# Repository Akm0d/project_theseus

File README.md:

# Project Theseus
This project is forked from the private repo of the OpenWest Defusal Station project. It is named "Project Theseus" after the paradox of the Ship of Theseus; a thought experiment that raises the question of whether an object that has had all of its components replaced remains fundamentally the same object.

# Contribution Guidelines
1. Create a branch for your code and merge it to master once the changes are stable
2. Keep the file structure as organized as possible
3. Never commit binaries, hidden files created by your IDE, or Windows-style line endings.
4. Keep detailed comments of what each function is meant to do
5. Follow the PEP-8 standard when writing python https://www.python.org/dev/peps/pep-0008/
6. Use comments starting with TODO to mark a feature that needs to be implemented and FIXME to mark features that need to be improved
7. If you are stuck, then it is absolutely OK to ask for help

# Getting Started
```bash
$ sudo apt-get update
$ sudo apt-get install python3 git python3-pip
$ git clone https://github.com/jtylers/project_theseus.git
$ cd project_theseus
$ git submodule update --init
$ pip3 install -r requirements.txt
$ ./serve.py
$ firefox 127.0.0.1:5000
```
I highly suggest using PyCharm if you are working with Flask and Python
```bash
$ sudo apt-get update
$ sudo apt-get install snapd
$ snap install pycharm-community
```
Add the project root to your python path for things to run correctly
```bash
$ echo "export PYTHONPATH=$PYTHONPATH:$HOME/project_theseus" >> ~/.profile
$ source ~/.profile
```

## Raspberry pi - ARCH Linux Setup
```bash
$ ## login with user: root password: root
$ # Delete default user
$ userdel alarm
$ # Create a new adminuser
$ useradd admin
$ # Set password for admin
$ passwd admin
$ # Make a home folder for admin
$ mkdir -p /home/admin
$ # Change ownership of the admin's home folder
$ chown -R admin:admin /home/admin
$ pacman -S sudo
$ # Grant admin sudo privileges
$ visudo
$ ## Press SHIFT + G then SHIFT + A
$ ## type "admin ALL=(ALL) ALL" without the quotes
$ ## save and quit by pressing ESCAPE, typing ":x" and pressing ENTER
$ # Remove root's password entry so that you can only log in as "admin" and use sudo and to do root stuff
$ vim /etc/shadow
$ ## replace root's password hash with !
$ # Install dependencies
$ pacman -S fakeroot gcc git i2c-tools make nginx packer python python-dateutil python-flask python-flask-restful python-pip tmux vim 
$ packer -S raspi-config
$ # Enable I2C 
$ echo "dtparam=i2c_arm=on"| sudo tee -a /boot/config.txt
$ sudo reboot
$ ## Log in as admin
$ ## Allow admin to access i2c
$ sudo chown admin:admin /dev/i2c*
$ ## Proceed with the instructions from the "Getting Started" section
$ ## Run project_theseus/pi_setup.sh
```

## Where are variables stored?
Stored in the database
```
ID
Name
Laser   -- Deprecated
Code
Color
Time    -- Stored as a datetime object but written at end of game
Success
```

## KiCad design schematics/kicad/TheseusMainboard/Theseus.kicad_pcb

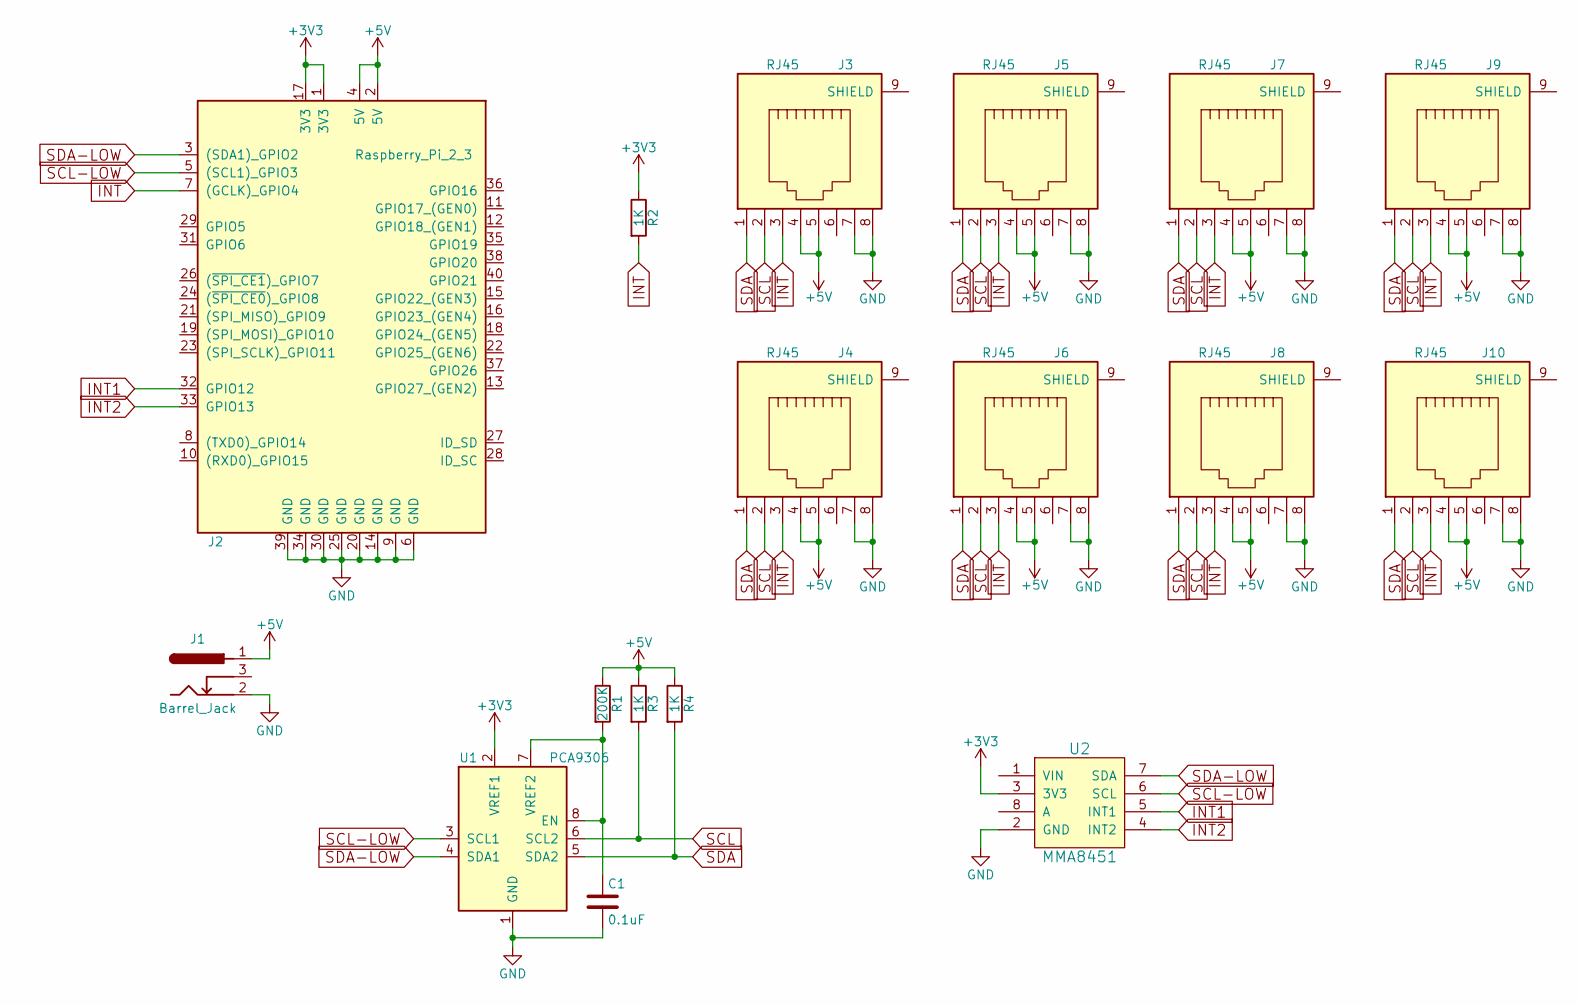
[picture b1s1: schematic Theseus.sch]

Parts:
C1: 0.1uF; C_0805_HandSoldering
J1: Barrel_Jack; POWER_JACK_PTH
J2: Raspberry_Pi_2_3; Pin_Header_Straight_2x20
J3, J4, J5, J6, J7, J8, J9, J10: RJ45; RJ45-8
R1: 200K; R_0805_HandSoldering
R2, R3, R4: 1K; R_0805_HandSoldering
U1: PCA9306; SO08
U2: MMA8451; Pin_Header_Straight_1x08_Pitch2.54mm

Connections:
+3V3: J2.1 (3V3), J2.17 (3V3), R2.1, U1.2 (VREF1), U2.3 (3V3)
+5V: J1.1, J2.2 (5V), J2.4 (5V), J3.4, J3.5, J4.4, J4.5, J5.4, J5.5, J6.4, J6.5, J7.4, J7.5, J8.4, J8.5, J9.4, J9.5, J10.4, J10.5, R1.1, R3.1, R4.1
GND: C1.2, J1.2, J2.6 (GND), J2.9 (GND), J2.14 (GND), J2.20 (GND), J2.25 (GND), J2.30 (GND), J2.34 (GND), J2.39 (GND), J3.7, J3.8, J4.7, J4.8, J5.7, J5.8, J6.7, J6.8, J7.7, J7.8, J8.7, J8.8, J9.7, J9.8, J10.7, J10.8, U1.1 (GND), U2.2 (GND)
INT: J2.7 ((GCLK)_GPIO4), J3.3, J4.3, J5.3, J6.3, J7.3, J8.3, J9.3, J10.3, R2.2
INT1: J2.32 (GPIO12), U2.5 (INT1)
INT2: J2.33 (GPIO13), U2.4 (INT2)
unnamed: C1.1, R1.2, U1.7 (VREF2), U1.8 (EN)
SCL: J3.2, J4.2, J5.2, J6.2, J7.2, J8.2, J9.2, J10.2, R3.2, U1.6 (SCL2)
SCL-LOW: J2.5 ((SCL1)_GPIO3), U1.3 (SCL1), U2.6 (SCL)
SDA: J3.1, J4.1, J5.1, J6.1, J7.1, J8.1, J9.1, J10.1, R4.2, U1.5 (SDA2)
SDA-LOW: J2.3 ((SDA1)_GPIO2), U1.4 (SDA1), U2.7 (SDA)

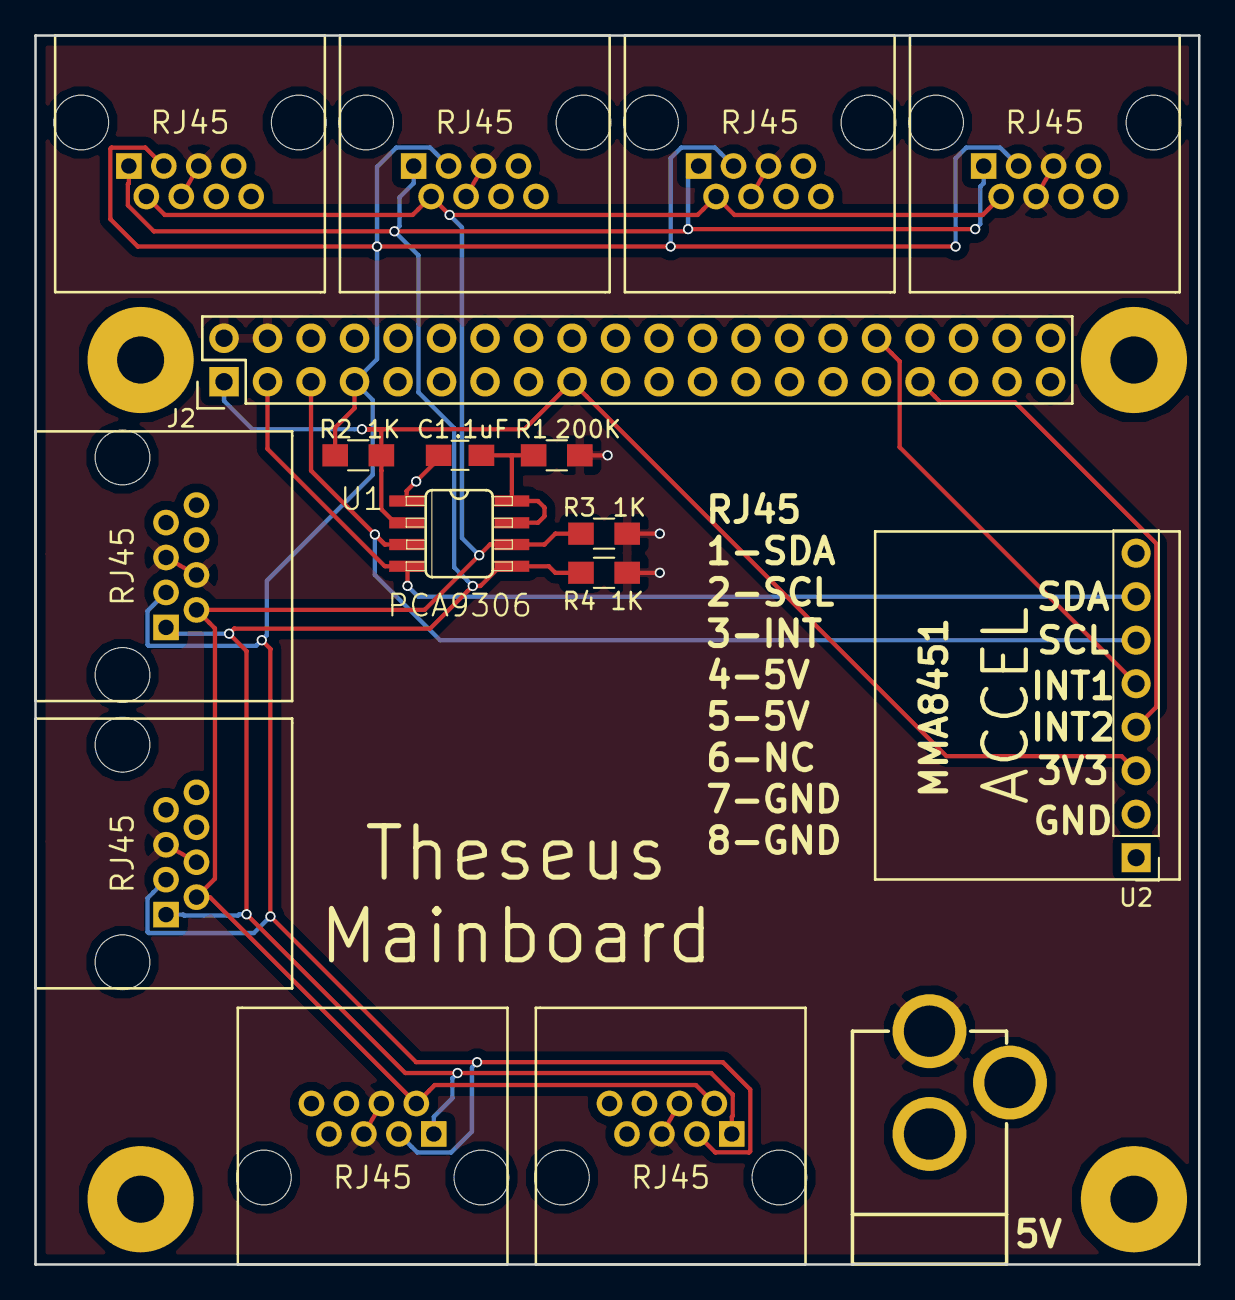
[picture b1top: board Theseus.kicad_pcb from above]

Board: 2 copper layers, 67.9 x 71.8 mm, 17 parts (0 on the bottom side), 11 nets.

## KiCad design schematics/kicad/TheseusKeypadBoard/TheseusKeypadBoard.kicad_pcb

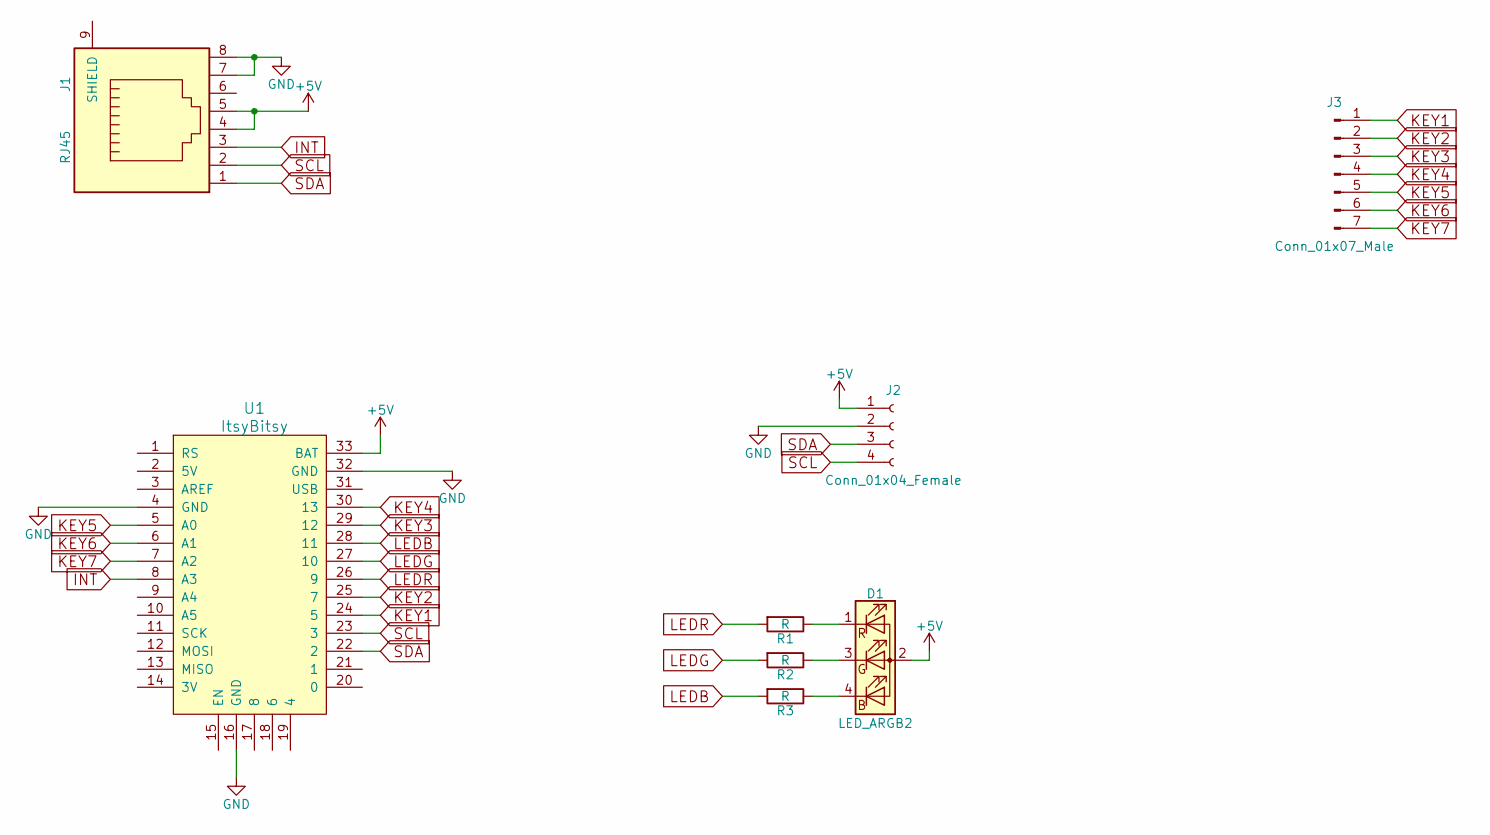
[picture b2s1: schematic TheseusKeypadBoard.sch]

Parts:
D1: LED_ARGB2
J1: RJ45; RJ45-8
J2: Conn_01x04_Female; Pin_Header_Straight_1x04_Pitch2.54mm
J3: Conn_01x07_Male; Pin_Header_Straight_1x07_Pitch2.54mm
R1, R2, R3: R; R_0805_HandSoldering
U1: ItsyBitsy

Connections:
+5V: D1.2 (A), J1.4, J1.5, J2.1, U1.33 (BAT)
GND: J1.7, J1.8, J2.2, U1.4 (GND), U1.16 (GND), U1.32 (GND)
INT: J1.3, U1.8 (A3)
KEY1: J3.1, U1.24 (5)
KEY2: J3.2, U1.25 (7)
KEY3: J3.3, U1.29 (12)
KEY4: J3.4, U1.30 (13)
KEY5: J3.5, U1.5 (A0)
KEY6: J3.6, U1.6 (A1)
KEY7: J3.7, U1.7 (A2)
LEDB: R3.2, U1.28 (11)
LEDG: R2.2, U1.27 (10)
LEDR: R1.2, U1.26 (9)
unnamed: D1.1 (RK), R1.1
unnamed: D1.3 (GK), R2.1
unnamed: D1.4 (BK), R3.1
SCL: J1.2, J2.4, U1.23 (3)
SDA: J1.1, J2.3, U1.22 (2)

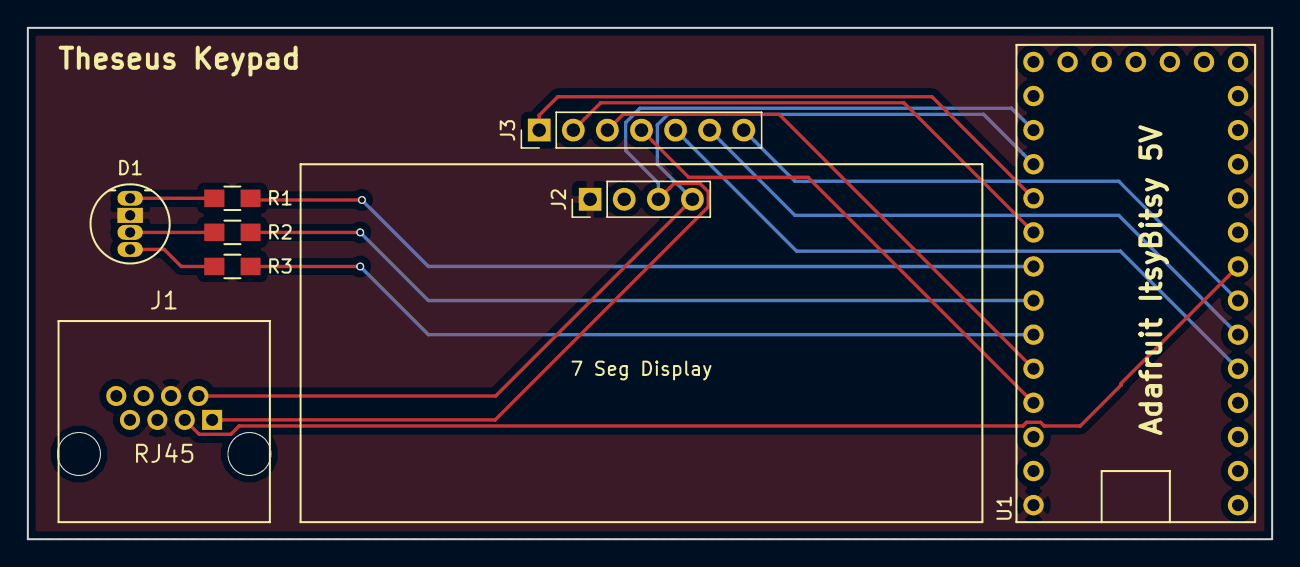
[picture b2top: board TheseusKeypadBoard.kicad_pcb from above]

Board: 2 copper layers, 92.7 x 38.1 mm, 8 parts (0 on the bottom side), 18 nets.

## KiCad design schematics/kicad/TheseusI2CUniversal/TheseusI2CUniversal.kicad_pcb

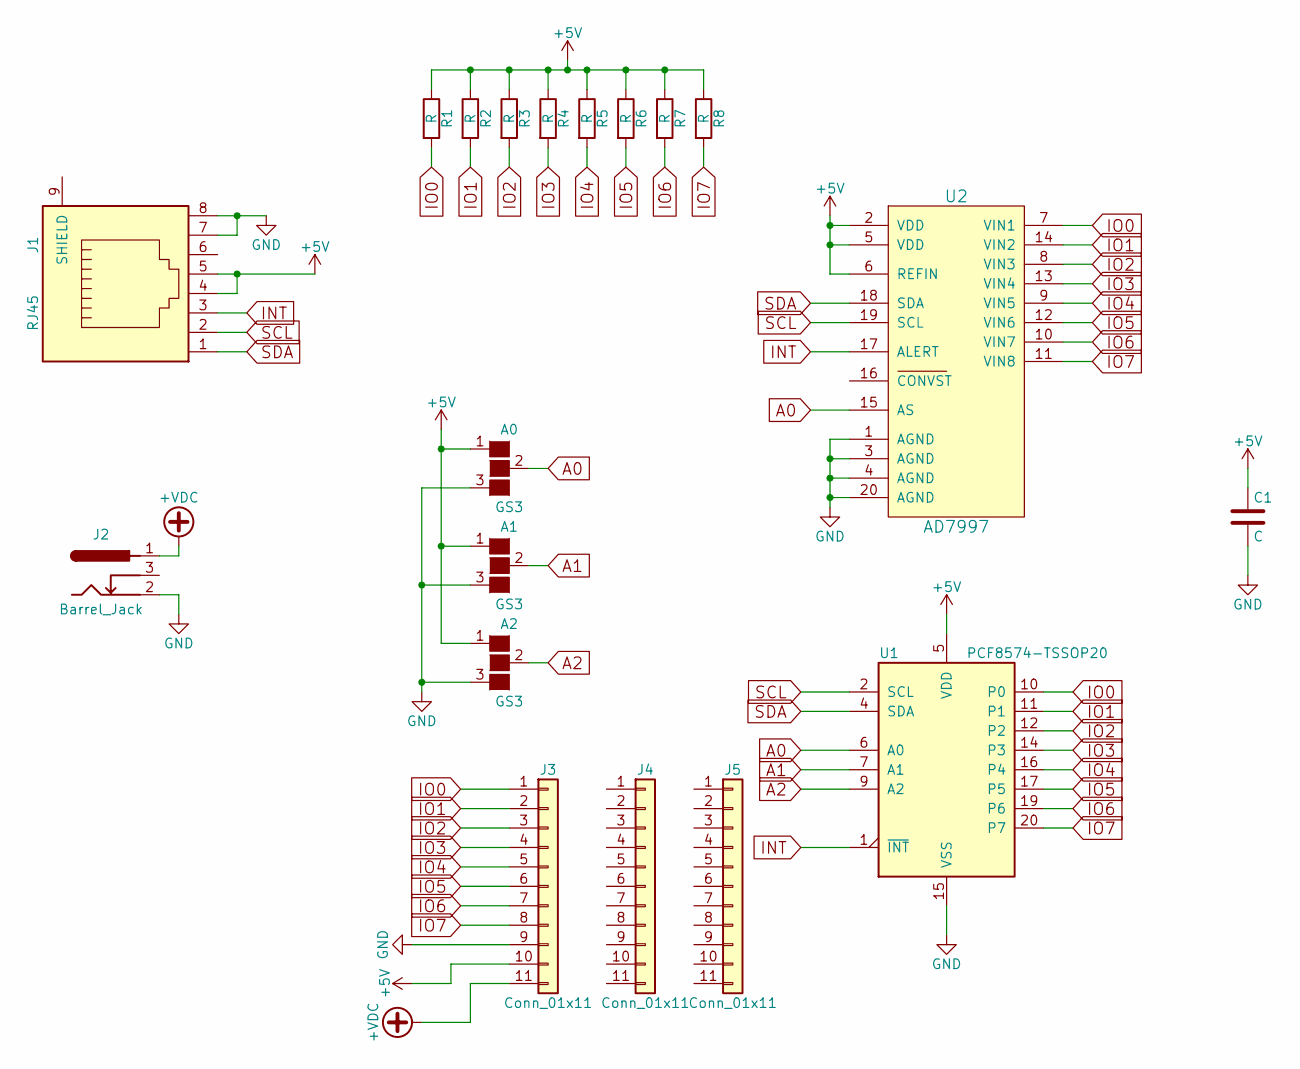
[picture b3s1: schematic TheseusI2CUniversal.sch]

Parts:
A0, A1, A2: GS3
C1: C; C_0805_HandSoldering
J1: RJ45; RJ45-8
J2: Barrel_Jack; POWER_JACK_PTH
J3, J4, J5: Conn_01x11; Socket_Strip_Straight_1x11_Pitch2.54mm
R1, R2, R3, R4, R5, R6, R7, R8: R; R_0805_HandSoldering
U1: PCF8574-TSSOP20; TSSOP20
U2: AD7997; TSSOP20

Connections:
+5V: A0.1 (G1), A1.1 (G1), A2.1 (G1), C1.1, J1.4, J1.5, J3.10, R1.1, R2.1, R3.1, R4.1, R5.1, R6.1, R7.1, R8.1, U1.5 (VDD), U2.2 (VDD), U2.5 (VDD), U2.6 (REFIN)
+VDC: J2.1, J3.11
A0: A0.2 (G2), U1.6 (A0), U2.15 (AS)
A1: A1.2 (G2), U1.7 (A1)
A2: A2.2 (G2), U1.9 (A2)
GND: A0.3 (G3), A1.3 (G3), A2.3 (G3), C1.2, J1.7, J1.8, J2.2, J3.9, U1.15 (VSS), U2.1 (AGND), U2.3 (AGND), U2.4 (AGND), U2.20 (AGND)
INT: J1.3, U1.1 (~INT~), U2.17 (ALERT)
IO0: J3.1, R1.2, U1.10 (P0), U2.7 (VIN1)
IO1: J3.2, R2.2, U1.11 (P1), U2.14 (VIN2)
IO2: J3.3, R3.2, U1.12 (P2), U2.8 (VIN3)
IO3: J3.4, R4.2, U1.14 (P3), U2.13 (VIN4)
IO4: J3.5, R5.2, U1.16 (P4), U2.9 (VIN5)
IO5: J3.6, R6.2, U1.17 (P5), U2.12 (VIN6)
IO6: J3.7, R7.2, U1.19 (P6), U2.10 (VIN7)
IO7: J3.8, R8.2, U1.20 (P7), U2.11 (VIN8)
SCL: J1.2, U1.2 (SCL), U2.19 (SCL)
SDA: J1.1, U1.4 (SDA), U2.18 (SDA)

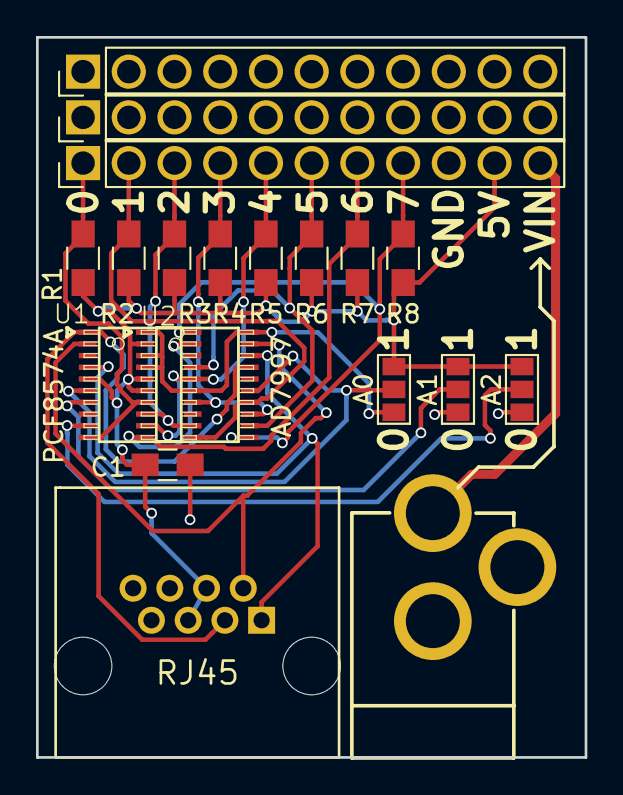
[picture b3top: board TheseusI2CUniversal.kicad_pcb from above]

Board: 2 copper layers, 30.5 x 40.0 mm, 19 parts (0 on the bottom side), 17 nets.

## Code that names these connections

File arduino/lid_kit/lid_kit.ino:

// Arduino code for project theseus
// Kristian Sims

#include <Keypad.h>
#include <Wire.h>

#define I2C_ADDRESS 0x69
#define KEYPAD_REGISTER = 0x23

// Set up keypad
#define NROWS 4
#define NCOLS 3
char keys[NROWS][NCOLS] = {
  {'1', '2', '3'},
  {'4', '5', '6'},
  {'7', '8', '9'},
  {'*', '0', '#'}
};
byte rows_pins[NROWS] = {5, 7, 12, 13};
byte cols_pins[NCOLS] = {A0, A1, A2};
Keypad keypad = Keypad(makeKeymap(keys), rows_pins, cols_pins, NROWS, NCOLS);

// Keypress buffer
#define BUFLEN 16
char key_buffer[BUFLEN];
int buffer_count = 0;

// LED Pins and 8-bit color scaling (which I made up, feel free to tweak)
#define LEDR 9
#define LEDG 10
#define LEDB 11

// Color maps for 8-bit color (vaguely logarithmic). Duty cycle is (255-x)/255.
byte led2bit[4] = {255, 191, 127, 0};  // 0%, 25%, 50%, 100%
byte led3bit[8] = {255, 223, 191, 159, 127, 63, 0, 0}; // w/e


void setup() {
  // Set up I2C as a slave
  Wire.begin(I2C_ADDRESS);
  Wire.onRequest(i2c_request);
  Wire.onReceive(i2c_receive);
  // Set up keypad. If you get duplicate keypress, increase debounce time. >200 is too much.
  keypad.setDebounceTime(50);
  keypad.addEventListener(keypad_event);
  Serial.begin(115200);
}

void loop() {
  keypad.getKey();
}

// On I2C read, return buffered characters, or a single "." for no keypress
void i2c_request() {
  Serial.write("KEY: ");
  if (buffer_count > 0) {
    Wire.write(key_buffer);
    Serial.write(key_buffer);
    // Clear buffer so string termination is automatic
    while (buffer_count > 0)
      key_buffer[--buffer_count] = 0;
  } else {
    Serial.write(key_buffer);
    Wire.write(".");
  }
  Serial.write("\n\r");
}

// On I2C write, receive a value and light the LED
// Note that the LED pins are 5 V to pin, so lower PWM is a brighter light.
void i2c_receive(int byte_count) {
  if (byte_count == 1) {
    // If 1 byte sent, interpret as analog color
    byte b = Wire.read();
    Serial.write("I2C: ");
    Serial.write(b);
    Serial.write("\n\r");
    analogWrite(LEDB, led2bit[b & 0x03]);
    b >>= 2;
    analogWrite(LEDG, led3bit[b & 0x07]);
    b >>= 3;
    analogWrite(LEDR, led3bit[b & 0x07]);
  } else if (byte_count == 3) {
    // If 3 bytes sent, interpret as raw values
    analogWrite(LEDR, 255 - Wire.read());
    analogWrite(LEDG, 255 - Wire.read());
    analogWrite(LEDB, 255 - Wire.read());
  } else {
    // Um, just ignore other byte counts, flush buffer
    while (Wire.available())
      Wire.read();
  }
}

// When a debounced keypress is detected, add it to the buffer
void keypad_event(KeypadEvent key) {
  if (keypad.getState() == PRESSED) {
    if (buffer_count < BUFLEN) {
      key_buffer[buffer_count++] = key;
    }
  }
}

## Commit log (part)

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2018-01-24 Forked from Defusal Station v1
2018-01-24 Added project name description
2018-01-25 Added minimal flask server
2018-01-25 Added basic flask
2018-01-25 ignore pycache directories
2018-01-25 removed IDE files
2018-01-25 updated requirements.txt
2018-01-25 require packages gt or eq to the given package versions
2018-01-25 restructured for easy templates
2018-01-25 Added instructions to readme
2018-01-27 Added api blueprint
2018-02-16 fixed readme
2018-02-18 Added basic admin page that has a few buttons
2018-02-19 function is no longer in-line so it can be called from onReady
2018-02-19 tripwires have full html functions
2018-02-19 prevent non-hex input
2018-02-19 Added color wheel selection to api
2018-02-19 Random calls the "tripwire-all" function to get status
2018-02-19 Moved admin resources to admin page
2018-02-21 if keycode is blank then return the current keycode
2018-02-22 blur inputs after changing them
2018-02-22 Removed create_app function
2018-02-22 Reformatted api
2018-02-22 Moved api functions from /admin to /api
2018-02-22 Added game logic
2018-02-22 Fork game logic
2018-02-22 removed register class
2018-02-22 fixed formatting to pep-8 standard
2018-02-22 Fixed pathing
2018-02-22 Fixed import
2018-02-22 Set up structure for mock libraries
2018-02-22 Added helpful comments
2018-02-22 Trimmed mock libraries to basic necessities
2018-02-22 Set precedence for properties
2018-02-22 Added rotating log handlers to all modules
2018-02-22 log messages use module name instead of path
2018-02-22 Don't delete old logs
2018-02-22 Added I2C requirements
2018-02-27 ignore atom IDE files
2018-03-01 added basic outlines
2018-03-02 Mock libraries work correctly
2018-03-03 The RPi2 uses i2c-1
2018-03-05 Write i2c block data instead of a single byte
2018-03-05 removed adafruit and mock dependencies
2018-03-09 Beefed up the database class
2018-03-09 hide execute from function hints
2018-04-07 Updated database to contain all columns - added database value setters to the game logic - wrote in a bunch of TODO for you to enjoy
2018-04-13 Last row of database is easily modifiable
2018-05-05 Fixes logging location
2018-05-05 Adds field to admin page to add new entry to scoreboard.
    Also changes jquery to open from local file, rather than from CDN so local running without network is possible.
    Adds proper url to __init__.py
    Adds resource to resources.py
2018-05-05 Running the program in a single thread, use pubsub for events
2018-05-05 Added command line arg for mock smbus
2018-05-05 Turns out we do need the fork
2018-05-05 Move all enums to same file
2018-05-05 import enum from constants
2018-05-05 Adds state property
2018-05-05 Created basic state machine
2018-05-05 Auto stash before merge of "master" and "origin/master"
2018-05-05 Adds /successes/ /attempts/ /high-scores/ /timer-text/
    successes provides a number of successes
    attempts provides a number of attempts
    high-scores will return a JSON of the top 5 teams
    timer-text returns timer text formatted like '00:00'
2018-05-06 Fixed CSS for homepage and admin
    - Added a pretty navbar
    - Touched up some js so that it is pulling from api
2018-05-06 Updated index.js
    - Leaderboard for highscores now updates per api
    - Logos of OpenWest and BYU-LC added to navbar
2018-05-06 Division
    - index.js correctly calculates the percentage of success
2018-05-06 Updates highscores url to provide time information.
    * Updates Resources.py to return dictionary of dictionaries about each entry
    * Updates index.html to have necessary id's for table data entries
    * Updates index.js to also update the timer code.
2018-05-06 Fix for admin.js
    - So it turns out that the mind doesn't let you go to bed unless you've solved that problem...and I did
2018-05-06 colors
    - made red same tone as all others
2018-05-06 Adds code necessary to simulate timer running while using --mock
    Adds timer variable to Logic
    Adds timer reduction in _run
    Adds mock variable in Logic to track if we are on the py
2018-05-06 RGB Select
    - It has now been formatted with bootstrap and admin.html is done for now, until we change some functionalities
2018-05-06 Remove duplicate timer functions, unified team name input to work the same as everything else on admin page
2018-05-07 Added time property
2018-05-07 FIX: saving work
2018-05-07 Separated state actions and state transitions
2018-05-07 Interprocess communication is working
2018-05-07 Finalizes multiprocess communication.
    * Creates Enum for the communication strings
    * Changes all instances of message sending to proper Enum
    * Creates constant INTERRUPTS_PER_SECOND for how many times _loop should run per second
    * Creates SLEEP_INTERVAL based on INTERRUPTS_PER_SECOND that tells Logic.run() how long to sleep between running _loop
    * Adds communication handling inside _loop
    * Adds code to run timer
2018-05-07 Adds comments to further clarify multiprocess communication
2018-05-07 Adds universal logging level as LOGGING_LEVEL.
    * Individual logging levels for individual files can still be set by changing what appears in that file's setLevel function.
2018-05-07 Updates index.js to make timer update every second, and everything else less often.
    The reasoning behind this is simple. It results in a much smoother timer, and we don't care about the high scores, attempts, and successes every second. It is doubtful these will change every second.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
2018-05-07 Log level set at command line
2018-05-07 Cleaned up state transition and action naming
2018-05-07 Updates to allow controlling solenoid from admin console.
2018-05-07 Clearly separated state actions and state transitions
2018-05-07 Fixed naming
2018-05-07 Removed outdated/un-needed files added new schematics
2018-05-07 Moved python to top-level
2018-05-08 Adds loglevel to run function to pass it to that process
2018-05-08 Updating and reading keycode from Logic() working
2018-05-09 Width change
    It needed to happen
2018-05-09 Updates Timer to uses JSCom
2018-05-09 Database prep
    Have more than 10 values in the database ready to implement filtering
2018-05-09 Connects ultrasonic to Logic()
2018-05-09 Database top 5
    - Returns successfully top 5 scores from legit database
2018-05-09 Configured logger correctly in all files - Fixed some Pep-008 formatting errors
2018-05-09 Database has constant path
2018-05-09 replaced max time with time given
2018-05-09 Removed TODO from database
2018-05-09 Optimized resource imports
2018-05-09 Admin page is fully funcitonal
2018-05-09 Add new row to the database on start game
2018-05-09 refresh_all after start game
2018-05-10 Use a single logger for everything
2018-05-10 Optimize imports
2018-05-10 Added QT gui to simulate box
2018-05-10 Added function to call UI
2018-05-10 switched from radio buttons to checkboxes
2018-05-10 Added lasers to gui
2018-05-10 added names to rgb
2018-05-10 Added frames and removed some checkability
2018-05-10 Create Qt Gui from serve.py with mock flack
2018-05-10 added qt5 to requirements
2018-05-10 created base UI object with TODOs
2018-05-10 Added example of function connecting to button
2018-05-15 Test mutliprocess dictionary in mockbus
2018-05-15 Cleaned up i2c library
2018-05-16 Using multiprocessing dict
2018-05-16 Logger exists
2018-05-16 For Chris
2018-05-16 Undid that silly thing
2018-05-16 Fixed that silly problem for good
2018-05-16 Using shared dict for everything
2018-05-16 Added clarification to requirements
2018-05-16 Timer works again
2018-05-16 Percentage fixed to display only one decimal
    - used toFixed method
2018-05-16 Cleaned up old code and fixed scoring
2018-05-16 Modifying last row works correctly
2018-05-16 Don't randomize things unecessarily
2018-05-16 Fixed formatting and max time
2018-05-16 Moved routes to __init__
2018-05-17 Fixed laser binary
2018-05-17 Updated page and made front page more responsive
2018-05-17 Refresh admin page every 1.5 seconds
2018-05-17 Fixed database imports
2018-05-17 Fixed start button value in all states
2018-05-18 Loop runs with the scheduler
2018-05-18 Cripple the apscheduler logger
2018-05-18 Added tripwires to mock box
2018-05-18 Send tripwire signals with gui
2018-05-18 Connected rotary encoder
2018-05-18 Connected Switches
2018-05-18 Added start reset button to mock box
2018-05-18 Removed mock GPIO
2018-05-18 Programmed mock reset button
2018-05-19 Reorganized GUI. prints are logs
2018-05-19 added apscheduler to requirements
2018-05-19 added pyqt5 to requirements
2018-05-21 Added ultrasonic sensor to gui
2018-05-22 created arduino code folder again
2018-05-22 Get ready to control seven seg
2018-05-24 UI expands properly
2018-05-25 MockBox Gui is easier to understand
2018-05-25 fixed simple spacing issue
2018-05-30 added i2c class
2018-05-30 Got rid of submodule
2018-05-30 fixed imports
2018-05-30 Typed everything
2018-05-30 MockBus is implemented correclty
2018-05-30 Optimized imports
2018-05-30 Mock elements are in same folder
2018-05-30 Moved arduino code to correct folder
2018-05-30 --mock will override smbus import
2018-05-30 Fixes errors with i2c and my code
2018-05-30 Fixes error in property code
2018-05-30 Fixes errors with old lasers object
2018-05-30 Override Mock GPIO
2018-05-30 Renamed MockPi folder
2018-05-30 Fixed intenum typecasting errors
2018-05-30 Fixes errors with lasers
2018-05-30 Mockbus might work
2018-05-30 Added Mock libraries and todo for i2c lib
2018-05-30 Mock SMBus works like regular smbus
2018-05-31 added lid kit
2018-05-31 updates to randomize and run lasers when game is done
2018-05-31 Fixes random button
2018-05-31 Updated constants to match reality
2018-05-31 I2c modules use constants
2018-05-31 Fixes lasers file
2018-05-31 Arduino code is up to date
2018-06-02 Restructured Lid kit class
2018-06-03 Sevengseg and lid kit are TWO SEPRATE I2C adresses
2018-06-03 Added Serial output for debugging
2018-06-03 Able to read and write from arduino I2c
2018-06-04 Added test code
2018-06-04 Fixing up mock stuff
2018-06-05 Remove mock stuff for now, also use smbus2 and such and things and .... yeahh......
2018-06-06 Adds laser code: TODO: Fix sevenseg.py
2018-06-06 Removed mock stuff, use smbus2
2018-06-06 Sevenseg code is functional
2018-06-06 Added i2c constants
2018-06-06 Added switch code, testing is a little more robust too, good stuff, makes my mamma proud :)
2018-06-07 Working keypad, revamped lasers, potentially working lock
2018-06-07 Fixed receptors
2018-06-07 Fixed laser and lidkit modules
2018-06-07 Fixed sevenseg addressing
2018-06-08 fixing logic.py
2018-06-08 Fixed receptor bug
2018-06-08 Fixed color bug in logic.py
2018-06-08 Starts game logic
2018-06-08 Test Suite is comprehensive
2018-06-08 Test suite is fully mmmmm
2018-07-14 Added api as submodule
2018-07-14 Moves API code to API folder
2018-07-14 Updated to newest commit of Project_Theseus_API
2018-07-17 Added instructions for updating submodule
2018-07-17 Use https for cloningsubmodules
    This is because the rpi used in the project won't have an ssh key
2018-07-17 Added magic bullet ipv6 script
2018-07-17 Added old link back as a comment
2018-07-17 Added instructions for settint up pi with ipv6
2018-07-17 Added pi setup instructions to readme
2018-07-17 format chagnes
2018-07-18 Added service files
2018-07-18 Created script to setup links
2018-07-18 Service mostly works now
2018-07-19 Don't try and read sensors if they are disconnected
2018-07-21 Updated qt stuff
2018-08-04 Zero Message Queue actually works mostly
2018-08-04 Updates version of API
2018-08-04 Updates to get laser updates in API
2018-08-04 Updates API to get updated receptor test
2018-08-04 Added code that kills player if time runs out or lasers are blocked
2018-09-12 Adds new ways to die!
    The switches now correspond with how the RGB LED lights up to indicate the proper keypad code.
    Typing in the wrong code kills the player.
    Blocking a laser will kill the player.
    TODO: The updateLed function makes some assumptions as to how the switches return. A verification needs to take place as this may not work as Graigry thought.
